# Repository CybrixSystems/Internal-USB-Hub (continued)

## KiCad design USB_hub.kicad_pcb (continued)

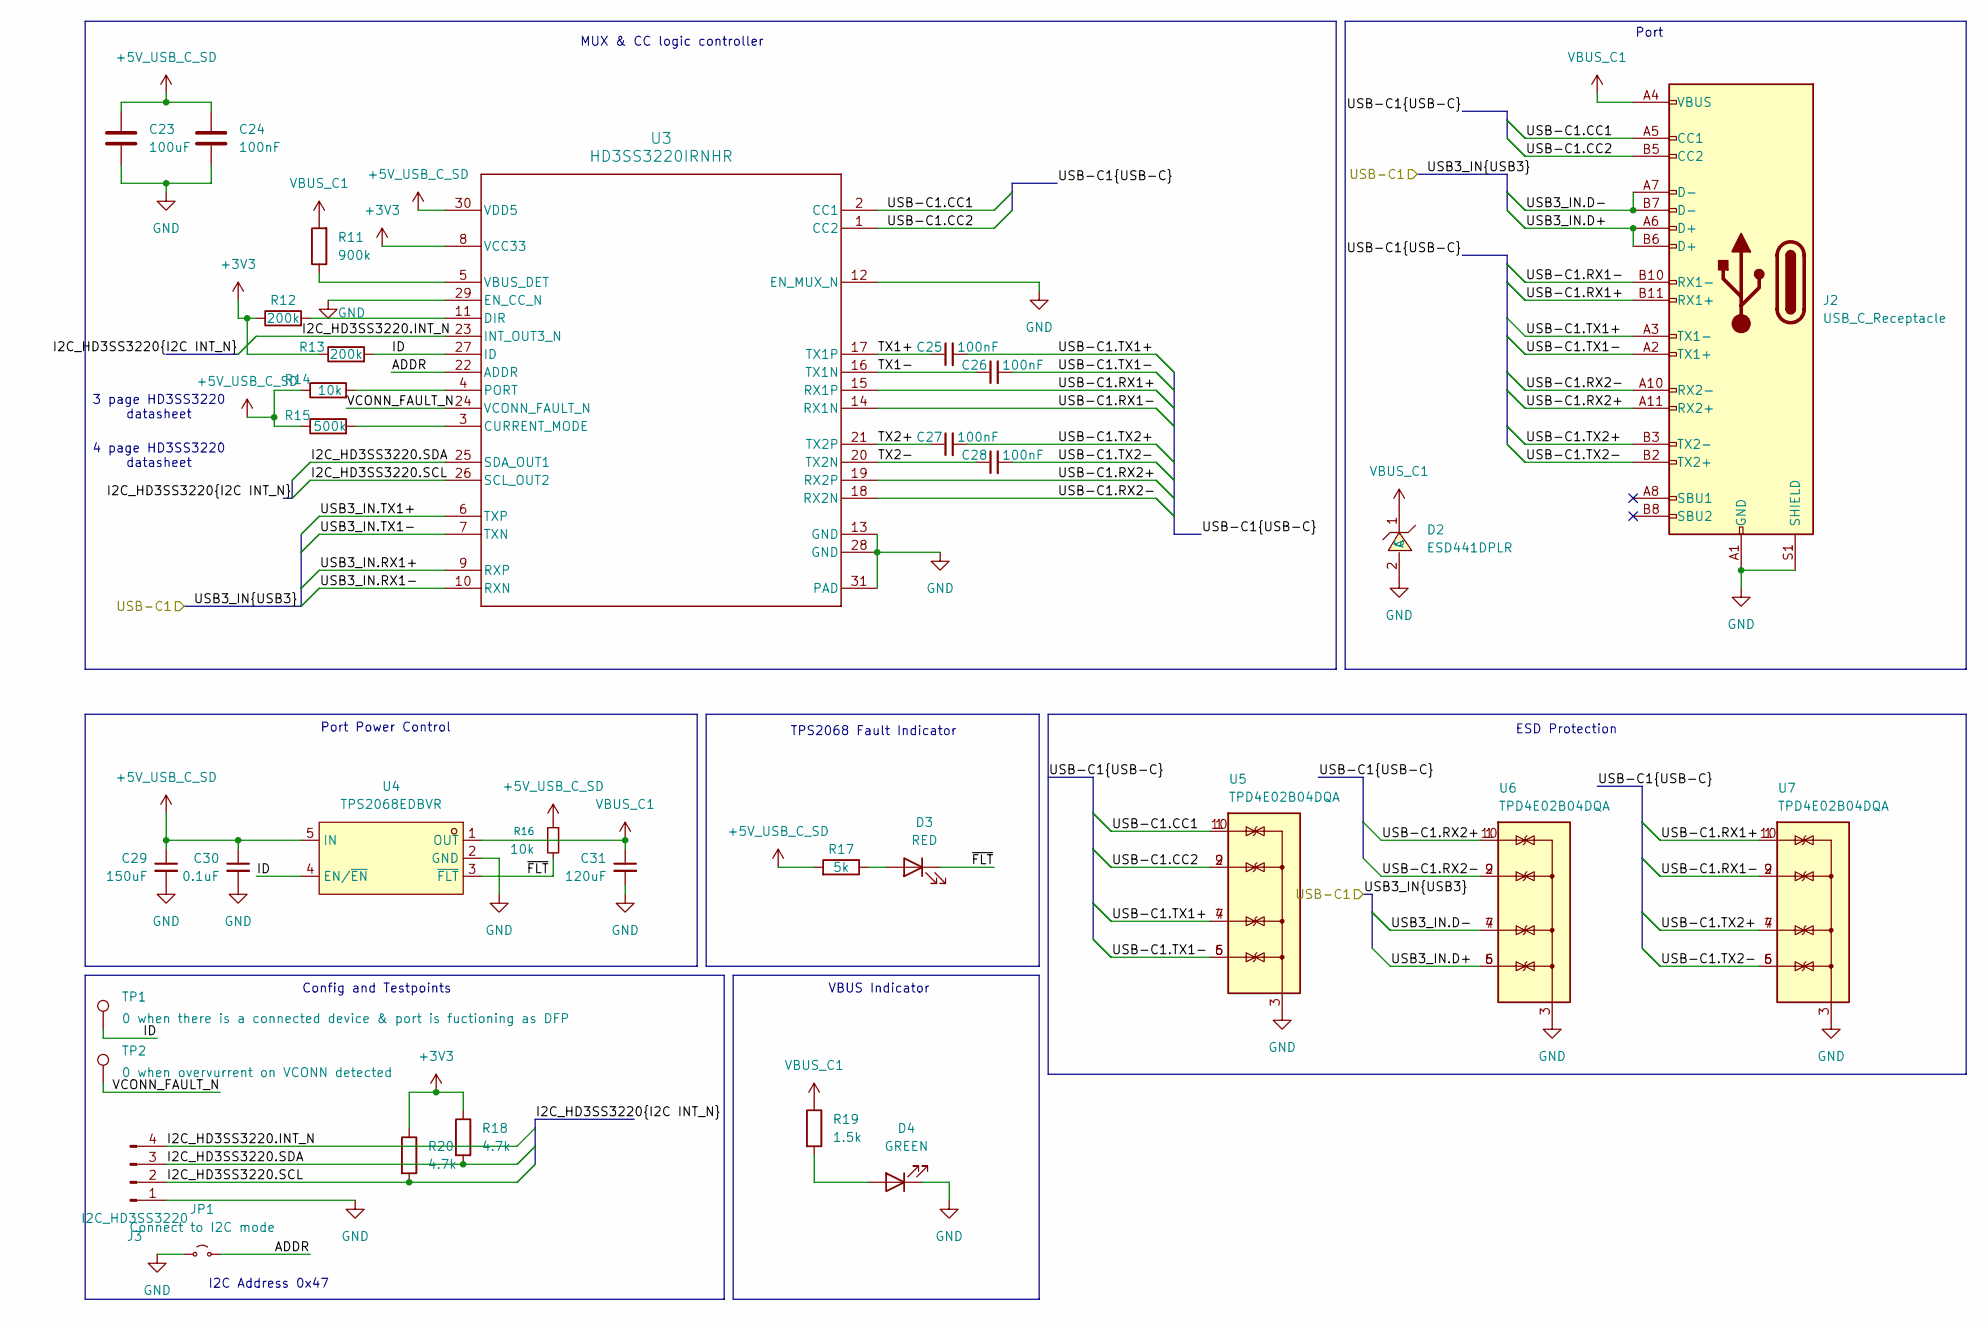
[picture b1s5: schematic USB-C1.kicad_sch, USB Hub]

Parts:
C23: 100uF; C_0805_2012Metric; LCSC Part C141660
C24, C25, C26, C27, C28: 100nF; C_0201_0603Metric; LCSC Part C181043
C29: 150uF; C_Radial_D6.3mm_H11.0mm_P2.50mm; LCSC Part C338186
C30: 0.1uF; C_0201_0603Metric; LCSC Part C181043
C31: 120uF; C_Radial_D6.3mm_H11.0mm_P2.50mm; LCSC Part C442816
D2: ESD441DPLR; X2SON-2_L0.6-W0.3-P0.35; LCSC Part C22427765
D3: RED; LED_0603_1608Metric; LCSC Part C497918
D4: GREEN; LED_0603_1608Metric; LCSC Part C22371298
J2: USB_C_Receptacle; USB420003A; Mouser Part No 640-USB4200-03-A
J3: I2C_HD3SS3220; PinHeader_1x04_P1.00mm_Vertical
JP1: Connect to I2C mode; SolderJumper-2_P1.3mm_Open_Pad1.0x1.5mm
R11: 900k; R_1206_3216Metric; Mouser Part No 603-RT1206CRE07900KL
R12, R13: 200k; R_0402_1005Metric; LCSC Part C25764
R14, R16: 10k; R_0402_1005Metric; LCSC Part C25744
R15: 500k; R_0603_1608Metric; LCSC Part C2902631
R17: 5k; R_0402_1005Metric; LCSC Part C5948099
R18, R20: 4.7k; R_0402_1005Metric; LCSC Part C105871
R19: 1.5k; R_0402_1005Metric; LCSC Part C327253
TP1: 0 when there is a connected device & port is fuct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; TestPoint_Pad_D1.0mm
TP2: 0 when overvurrent on VCONN detected; TestPoint_Pad_D1.0mm
U3: HD3SS3220IRNHR; RNH0030A; LCSC Part C165155
U4: TPS2068EDBVR; TSOT-23-5_L2.9-W1.6-P0.95-LS2.8-BR; LCSC Part C19272843
U5, U6, U7: TPD4E02B04DQA; USON-10_2.5x1.0mm_P0.5mm; LCSC Part C106794

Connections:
+3V3: R12.1, R13.1, R18.1, R20.1, U3.8 (VCC33); also elsewhere on the board
+5V_USB_C_SD: C23.1, C24.1, C29.1, C30.1, R14.1, R15.1, R16.1, R17.2, U3.30 (VDD5), U4.5 (IN); also elsewhere on the board
/USB-C1/ADDR: JP1.2 (B), U3.22 (ADDR)
/USB-C1/I2C_HD3SS3220.INT_N: J3.4, U3.23 (INT_OUT3_N)
/USB-C1/I2C_HD3SS3220.SCL: J3.2, R20.2, U3.26 (SCL_OUT2)
/USB-C1/I2C_HD3SS3220.SDA: J3.3, R18.2, U3.25 (SDA_OUT1)
/USB-C1/ID: R13.2, TP1.1, U3.27 (ID), U4.4 (EN/~EN)
/USB-C1/TX1+: C25.1, U3.17 (TX1P)
/USB-C1/TX1-: C26.1, U3.16 (TX1N)
/USB-C1/TX2+: C27.1, U3.21 (TX2P)
/USB-C1/TX2-: C28.1, U3.20 (TX2N)
/USB-C1/USB3_IN.D+: J2.A6 (D+), J2.B6 (D+), U6.5 (IO4), U6.6 (NC); also elsewhere on the board
/USB-C1/USB3_IN.D-: J2.A7 (D-), J2.B7 (D-), U6.4 (IO3), U6.7 (NC); also elsewhere on the board
/USB-C1/USB3_IN.RX1+: U3.9 (RXP); also elsewhere on the board
/USB-C1/USB3_IN.RX1-: U3.10 (RXN); also elsewhere on the board
/USB-C1/USB3_IN.TX1+: U3.6 (TXP); also elsewhere on the board
/USB-C1/USB3_IN.TX1-: U3.7 (TXN)
/USB-C1/USB-C1.CC1: J2.A5 (CC1), U3.2 (CC1), U5.1 (IO1), U5.10 (NC)
/USB-C1/USB-C1.CC2: J2.B5 (CC2), U3.1 (CC2), U5.2 (IO2), U5.9 (NC)
/USB-C1/USB-C1.RX1+: J2.B11 (RX1+), U3.15 (RX1P), U7.1 (IO1), U7.10 (NC)
/USB-C1/USB-C1.RX1-: J2.B10 (RX1-), U3.14 (RX1N), U7.2 (IO2), U7.9 (NC)
/USB-C1/USB-C1.RX2+: J2.A11 (RX2+), U3.19 (RX2P), U6.1 (IO1), U6.10 (NC)
/USB-C1/USB-C1.RX2-: J2.A10 (RX2-), U3.18 (RX2N), U6.2 (IO2), U6.9 (NC)
/USB-C1/USB-C1.TX1+: C25.2, J2.A3 (TX1-), U5.4 (IO3), U5.7 (NC)
/USB-C1/USB-C1.TX1-: C26.2, J2.A2 (TX1+), U5.5 (IO4), U5.6 (NC)
/USB-C1/USB-C1.TX2+: C27.2, J2.B3 (TX2-), U7.4 (IO3), U7.7 (NC)
/USB-C1/USB-C1.TX2-: C28.2, J2.B2 (TX2+), U7.5 (IO4), U7.6 (NC)
/USB-C1/VCONN_FAULT_N: TP2.1, U3.24 (VCONN_FAULT_N)
/USB-C1/~FLT: D3.1 (K), R16.2, U4.3 (~FLT)
GND: C23.2, C24.2, C29.2, C30.2, C31.2, D2.2 (A), D4.1 (K), J2.A1 (GND), J2.A12 (GND), J2.B1 (GND), J2.B12 (GND), J2.S1 (SHIELD), J3.1, JP1.1 (A), U3.12 (EN_MUX_N), U3.13 (GND), U3.28 (GND), U3.29 (EN_CC_N), U3.31 (PAD), U4.2 (GND), U5.3 (G), U5.8 (G), U6.3 (G), U6.8 (G), U7.3 (G), U7.8 (G); also elsewhere on the board
unnamed: D3.2 (A), R17.1
unnamed: D4.2 (A), R19.2
unnamed: R15.2, U3.3 (CURRENT_MODE)
unnamed: R12.2, U3.11 (DIR)
unnamed: R14.2, U3.4 (PORT)
unnamed: R11.1, U3.5 (VBUS_DET)
VBUS_C1: C31.1, D2.1 (C), J2.A4 (VBUS), J2.A9 (VBUS), J2.B4 (VBUS), J2.B9 (VBUS), R11.2, R19.1, U4.1 (OUT); also elsewhere on the board

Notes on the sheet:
TPS2068 Fault Indicator
4 page HD3SS3220 datasheet
I2C Address 0x47
3 page HD3SS3220 datasheet
Port
VBUS Indicator
Config and Testpoints
Port Power Control
ESD Protection
MUX & CC logic controller

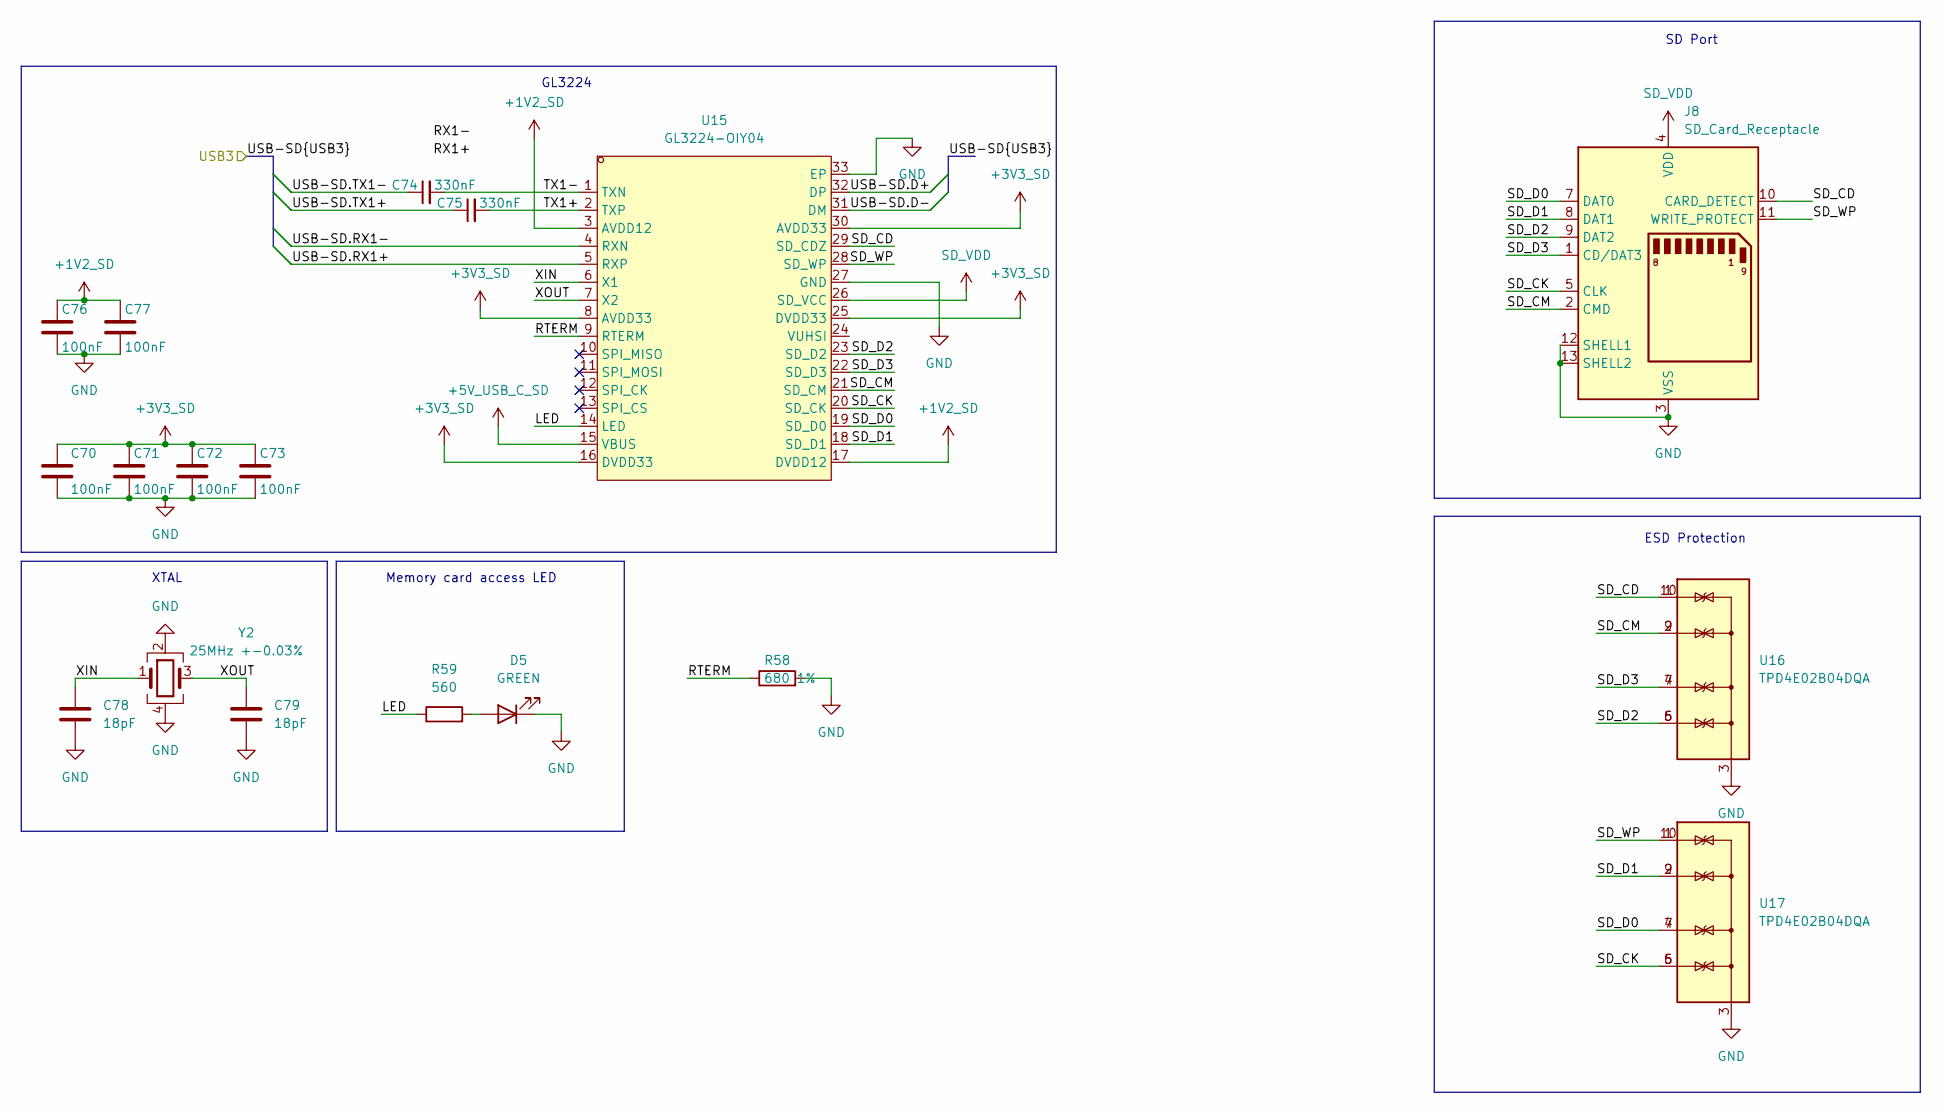
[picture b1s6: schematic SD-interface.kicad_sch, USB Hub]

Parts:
C70, C71, C72, C73, C76, C77: 100nF; C_0201_0603Metric; LCSC Part C181043
C74, C75: 330nF; C_0201_0603Metric; LCSC Part C2980695
C78, C79: 18pF; C_0402_1005Metric; LCSC Part C33149
D5: GREEN; LED_0603_1608Metric; LCSC Part C22371298
J8: SD_Card_Receptacle; SD2A; Mouser Part No 179-SD-2-A
R58: 680 1%; R_0402_1005Metric; LCSC Part C25130
R59: 560; R_0402_1005Metric; LCSC Part C137858
U15: GL3224-OIY04; HQFN-32_L5.0-W5.0-P0.50-BL-EP3.0; LCSC Part C157357
U16, U17: TPD4E02B04DQA; USON-10_2.5x1.0mm_P0.5mm; LCSC Part C106794
Y2: 25MHz +-0.03%; Crystal_SMD_3225-4Pin_3.2x2.5mm; LCSC Part C179643

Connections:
+1V2_SD: C76.1, C77.1, U15.3 (AVDD12), U15.17 (DVDD12)
+3V3_SD: C70.1, C71.1, C72.1, C73.1, U15.8 (AVDD33), U15.16 (DVDD33), U15.25 (DVDD33), U15.30 (AVDD33)
+5V_USB_C_SD: U15.15 (VBUS); also elsewhere on the board
/SD-interface/LED: R59.1, U15.14 (LED)
/SD-interface/RTERM: R58.1, U15.9 (RTERM)
/SD-interface/SD_CD: J8.10 (CARD_DETECT), U15.29 (SD_CDZ), U16.1 (IO1), U16.10 (NC)
/SD-interface/SD_CK: J8.5 (CLK), U15.20 (SD_CK), U17.5 (IO4), U17.6 (NC)
/SD-interface/SD_CM: J8.2 (CMD), U15.21 (SD_CM), U16.2 (IO2), U16.9 (NC)
/SD-interface/SD_D0: J8.7 (DAT0), U15.19 (SD_D0), U17.4 (IO3), U17.7 (NC)
/SD-interface/SD_D1: J8.8 (DAT1), U15.18 (SD_D1), U17.2 (IO2), U17.9 (NC)
/SD-interface/SD_D2: J8.9 (DAT2), U15.23 (SD_D2), U16.5 (IO4), U16.6 (NC)
/SD-interface/SD_D3: J8.1 (CD/DAT3), U15.22 (SD_D3), U16.4 (IO3), U16.7 (NC)
/SD-interface/SD_WP: J8.11 (WRITE_PROTECT), U15.28 (SD_WP), U17.1 (IO1), U17.10 (NC)
/SD-interface/TX1+: C75.2, U15.2 (TXP)
/SD-interface/TX1-: C74.2, U15.1 (TXN)
/SD-interface/USB-SD.D+: U15.32 (DP); also elsewhere on the board
/SD-interface/USB-SD.D-: U15.31 (DM); also elsewhere on the board
/SD-interface/USB-SD.RX1+: U15.5 (RXP); also elsewhere on the board
/SD-interface/USB-SD.RX1-: U15.4 (RXN); also elsewhere on the board
/SD-interface/USB-SD.TX1+: C75.1; also elsewhere on the board
/SD-interface/USB-SD.TX1-: C74.1; also elsewhere on the board
/SD-interface/XIN: C78.2, U15.6 (X1), Y2.1
/SD-interface/XOUT: C79.2, U15.7 (X2), Y2.3
GND: C70.2, C71.2, C72.2, C73.2, C76.2, C77.2, C78.1, C79.1, D5.1 (K), J8.3 (VSS), J8.6 (VSS), J8.12 (SHELL1), J8.13 (SHELL2), R58.2, U15.27 (GND), U15.33 (EP), U16.3 (G), U16.8 (G), U17.3 (G), U17.8 (G), Y2.2, Y2.4; also elsewhere on the board
unnamed: D5.2 (A), R59.2
SD_VDD: J8.4 (VDD), U15.26 (SD_VCC)

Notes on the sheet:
Memory card access LED
ESD Protection
SD Port
GL3224
XTAL

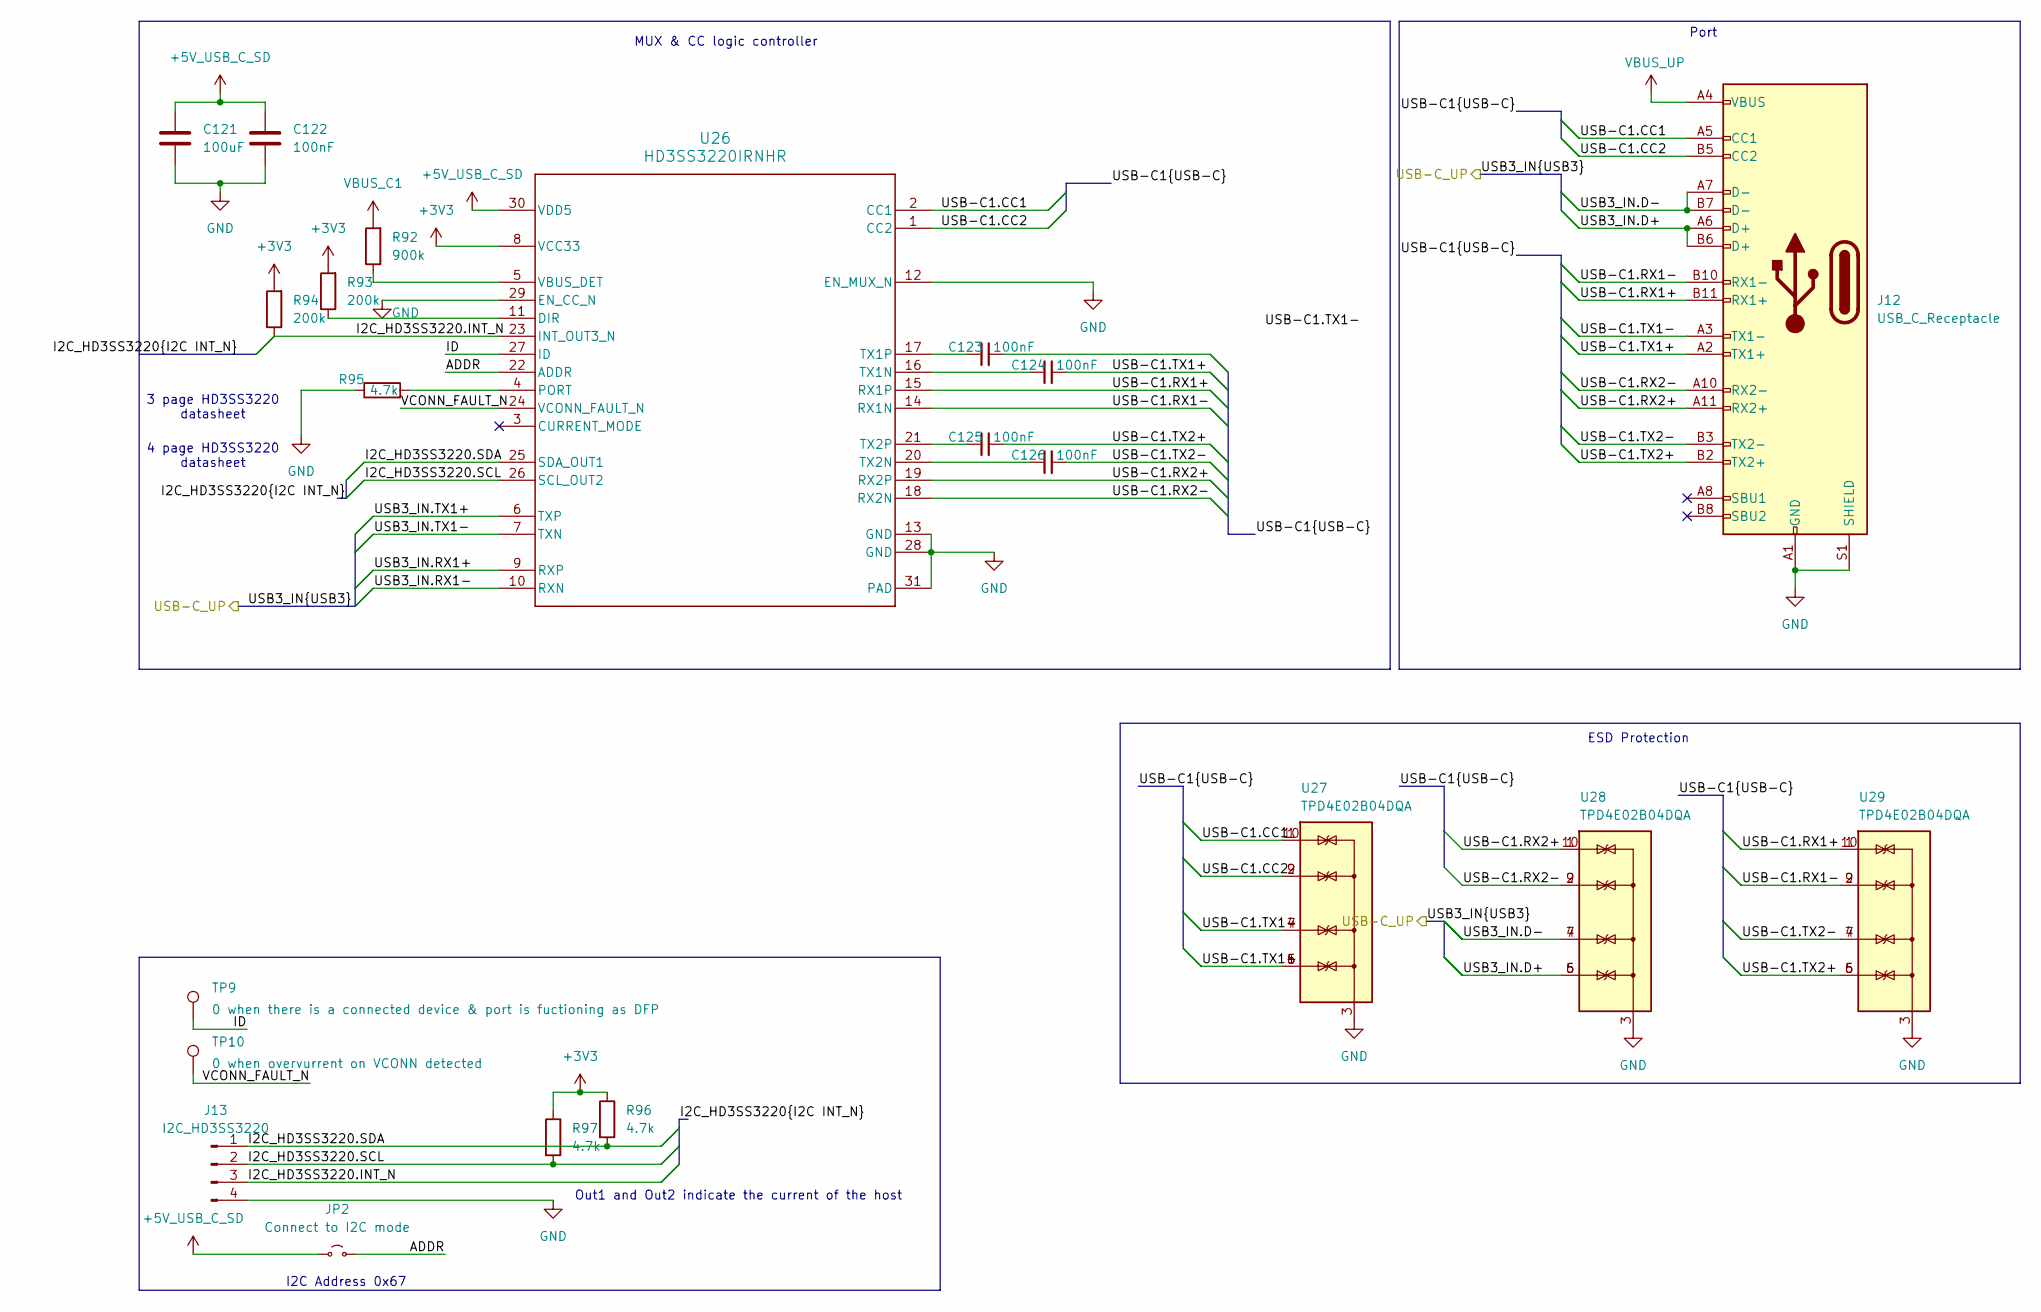
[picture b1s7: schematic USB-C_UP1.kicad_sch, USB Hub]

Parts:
C121: 100uF; C_0805_2012Metric; LCSC Part C141660
C122, C123, C124, C125, C126: 100nF; C_0201_0603Metric; LCSC Part C181043
J12: USB_C_Receptacle; USB_C_Receptacle_Amphenol_12401610E4-2A
J13: I2C_HD3SS3220; PinHeader_1x03_P1.00mm_Vertical
JP2: Connect to I2C mode; SolderJumper-2_P1.3mm_Open_RoundedPad1.0x1.5mm
R92: 900k; R_1206_3216Metric; Mouser Part No 603-RT1206CRE07900KL
R93, R94: 200k; R_0402_1005Metric; LCSC Part C25764
R95, R96, R97: 4.7k; R_0402_1005Metric; LCSC Part C105871
TP9: 0 when there is a connected device & port is fuct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; TestPoint_Pad_D1.0mm
TP10: 0 when overvurrent on VCONN detected; TestPoint_Pad_D1.0mm
U26: HD3SS3220IRNHR; RNH0030A; LCSC Part C165155
U27, U28, U29: TPD4E02B04DQA; USON-10_2.5x1.0mm_P0.5mm; LCSC Part C106794

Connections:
+3V3: R93.2, R94.2, R96.1, R97.1, U26.8 (VCC33); also elsewhere on the board
+5V_USB_C_SD: C121.1, C122.1, JP2.1 (A), U26.30 (VDD5); also elsewhere on the board
/USB-C_UP1/ADDR: JP2.2 (B), U26.22 (ADDR)
/USB-C_UP1/I2C_HD3SS3220.INT_N: J13.3, R94.1, U26.23 (INT_OUT3_N)
/USB-C_UP1/I2C_HD3SS3220.SCL: J13.2, R97.2, U26.26 (SCL_OUT2)
/USB-C_UP1/I2C_HD3SS3220.SDA: J13.1, R96.2, U26.25 (SDA_OUT1)
/USB-C_UP1/ID: TP9.1, U26.27 (ID)
/USB-C_UP1/USB3_IN.D+: J12.A6 (D+), J12.B6 (D+), U28.5 (IO4), U28.6 (NC); also elsewhere on the board
/USB-C_UP1/USB3_IN.D-: J12.A7 (D-), J12.B7 (D-), U28.4 (IO3), U28.7 (NC); also elsewhere on the board
/USB-C_UP1/USB3_IN.RX1+: U26.9 (RXP); also elsewhere on the board
/USB-C_UP1/USB3_IN.RX1-: U26.10 (RXN); also elsewhere on the board
/USB-C_UP1/USB3_IN.TX1+: U26.6 (TXP); also elsewhere on the board
/USB-C_UP1/USB3_IN.TX1-: U26.7 (TXN); also elsewhere on the board
/USB-C_UP1/USB-C1.CC1: J12.A5 (CC1), U26.2 (CC1), U27.1 (IO1), U27.10 (NC)
/USB-C_UP1/USB-C1.CC2: J12.B5 (CC2), U26.1 (CC2), U27.2 (IO2), U27.9 (NC)
/USB-C_UP1/USB-C1.RX1+: J12.B11 (RX1+), U26.15 (RX1P), U29.1 (IO1), U29.10 (NC)
/USB-C_UP1/USB-C1.RX1-: J12.B10 (RX1-), U26.14 (RX1N), U29.2 (IO2), U29.9 (NC)
/USB-C_UP1/USB-C1.RX2+: J12.A11 (RX2+), U26.19 (RX2P), U28.1 (IO1), U28.10 (NC)
/USB-C_UP1/USB-C1.RX2-: J12.A10 (RX2-), U26.18 (RX2N), U28.2 (IO2), U28.9 (NC)
/USB-C_UP1/USB-C1.TX1+: C124.2, J12.A2 (TX1+), U27.5 (IO4), U27.6 (NC)
/USB-C_UP1/USB-C1.TX1-: J12.A3 (TX1-), U27.4 (IO3), U27.7 (NC)
/USB-C_UP1/USB-C1.TX2+: C125.2, J12.B2 (TX2+), U29.5 (IO4), U29.6 (NC)
/USB-C_UP1/USB-C1.TX2-: C126.2, J12.B3 (TX2-), U29.4 (IO3), U29.7 (NC)
/USB-C_UP1/VCONN_FAULT_N: TP10.1, U26.24 (VCONN_FAULT_N)
GND: C121.2, C122.2, J12.A1 (GND), J12.A12 (GND), J12.B1 (GND), J12.B12 (GND), J12.S1 (SHIELD), J13.4, R95.1, U26.12 (EN_MUX_N), U26.13 (GND), U26.28 (GND), U26.29 (EN_CC_N), U26.31 (PAD), U27.3 (G), U27.8 (G), U28.3 (G), U28.8 (G), U29.3 (G), U29.8 (G); also elsewhere on the board
unnamed: R93.1, U26.11 (DIR)
unnamed: R95.2, U26.4 (PORT)
unnamed: C124.1, U26.16 (TX1N)
unnamed: C123.1, U26.17 (TX1P)
unnamed: C126.1, U26.20 (TX2N)
unnamed: C125.1, U26.21 (TX2P)
unnamed: R92.1, U26.5 (VBUS_DET)
VBUS_C1: R92.2; also elsewhere on the board
VBUS_UP: J12.A4 (VBUS), J12.A9 (VBUS), J12.B4 (VBUS), J12.B9 (VBUS); also elsewhere on the board

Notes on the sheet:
4 page HD3SS3220 datasheet
3 page HD3SS3220 datasheet
Port
Out1 and Out2 indicate the current of the host
I2C Address 0x67
ESD Protection
MUX & CC logic controller

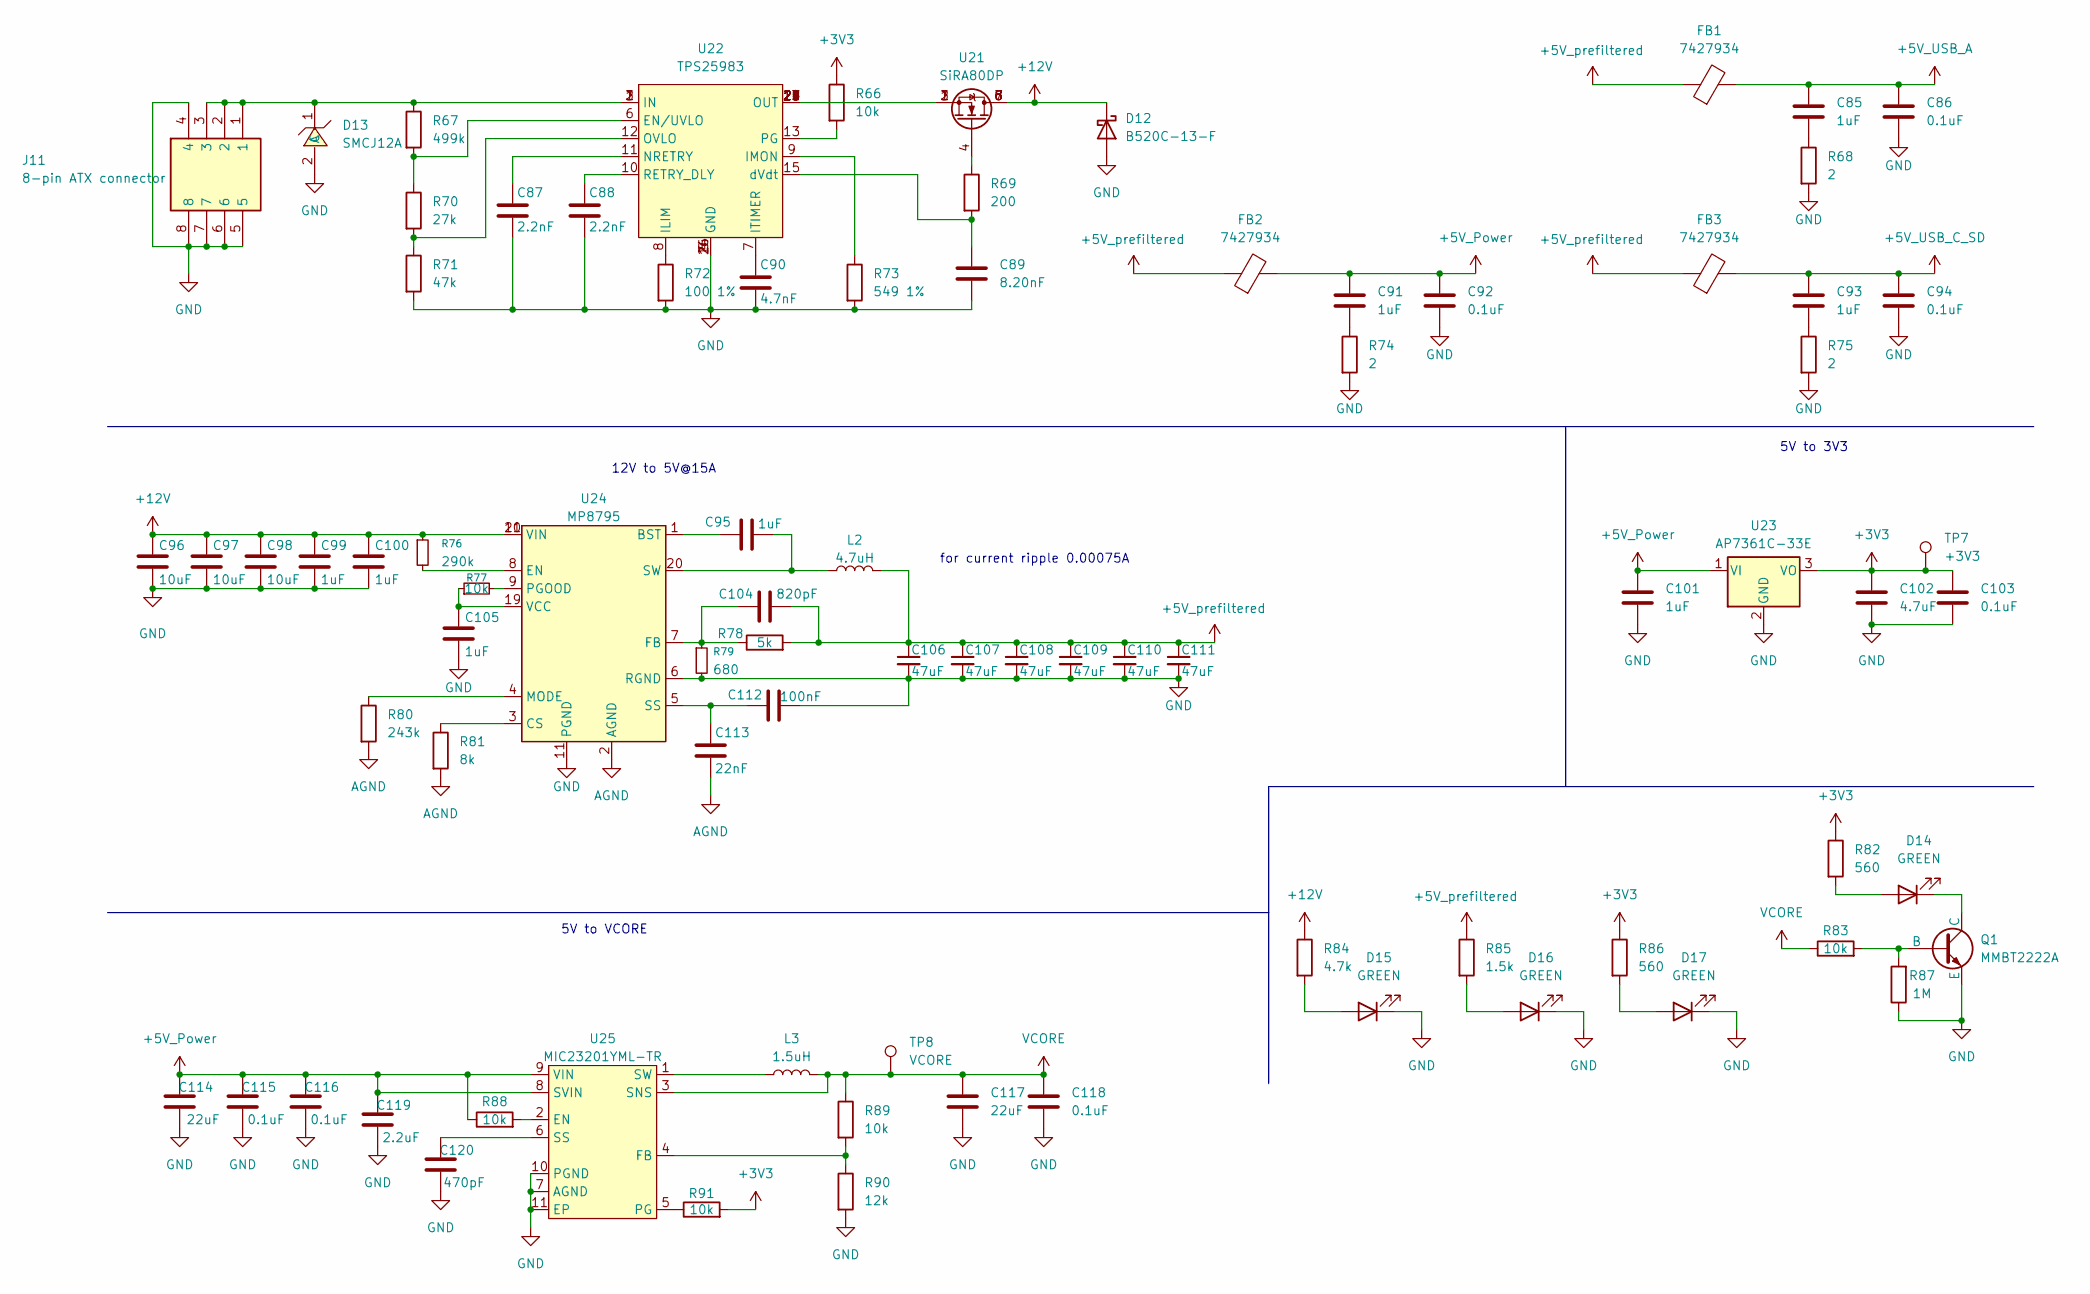
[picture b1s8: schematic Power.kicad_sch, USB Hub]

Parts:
C85, C91, C93, C95, C99, C100, C101, C105: 1uF; C_0603_1608Metric; LCSC Part C5199872
C86, C92, C94, C103, C115, C116, C118: 0.1uF; C_0201_0603Metric; LCSC Part C181043
C87, C88: 2.2nF; C_0402_1005Metric; LCSC Part C513667
C89: 8.20nF; C_0402_1005Metric; LCSC Part C541457
C90: 4.7nF; C_0402_1005Metric; LCSC Part C281757
C96, C97, C98: 10uF; C_0805_2012Metric; LCSC Part C3039694
C102: 4.7uF; C_0805_2012Metric; LCSC Part C6119944
C104: 820pF; C_0402_1005Metric; LCSC Part C114386
C106, C107, C108, C109, C110, C111: 47uF; C_Radial_D5.0mm_H11.0mm_P2.00mm; LCSC Part C721300
C112: 100nF; C_0201_0603Metric; LCSC Part C181043
C113: 22nF; C_0402_1005Metric; LCSC Part C77023
C114, C117: 22uF; C_1812_4532Metric; LCSC Part C141660
C119: 2.2uF; C_0402_1005Metric; LCSC Part C2999759
C120: 470pF; C_0402_1005Metric; LCSC Part C272887
D12: B520C-13-F; D_SMC; LCSC Part C134460
D13: SMCJ12A; D_SMC; LCSC Part C224038
D14, D15, D16, D17: GREEN; LED_0603_1608Metric; LCSC Part C22371298
FB1, FB2, FB3: 7427934; Mouser Part No 710-7427934; LCSC Part C5429469
J11: 8-pin ATX connector; 45586-000Y; Manufacturer_Part_Number 45586-0005; Mouser Part No 538-45586-0005
L2: 4.7uH; L_Coilcraft_XAL1010-XXX; LCSC Part C18199458
L3: 1.5uH; L_6.3x6.3_H3; LCSC Part C520330
Q1: MMBT2222A; SOT-23-3; LCSC Part C82460
R66, R77, R83, R88, R89, R91: 10k; R_0402_1005Metric; LCSC Part C25744
R67: 499k; R_0402_1005Metric; LCSC Part C137971
R68, R74, R75: 2; R_0603_1608Metric; LCSC Part C2907139
R69: 200; R_0402_1005Metric; LCSC Part C114764
R70: 27k; R_0402_1005Metric; LCSC Part C138022
R71: 47k; R_0402_1005Metric; LCSC Part C93943
R72: 100 1%; R_0402_1005Metric; LCSC Part C106232
R73: 549 1%; R_0402_1005Metric; LCSC Part C7334458
R76: 290k; R_0402_1005Metric; LCSC Part C5126158
R78: 5k; R_0402_1005Metric; LCSC Part C5948099
R79: 680; R_0402_1005Metric; LCSC Part C25130
R80: 243k; R_0402_1005Metric; LCSC Part C2998149
R81: 8k; R_0603_1608Metric; LCSC Part C862307
R82, R86: 560; R_0402_1005Metric; LCSC Part C137858
R84: 4.7k; R_0402_1005Metric; LCSC Part C105871
R85: 1.5k; R_0402_1005Metric; LCSC Part C327253
R87: 1M; R_0402_1005Metric; LCSC Part C2906900
R90: 12k; R_0402_1005Metric; LCSC Part C413006
TP7: +3V3; TestPoint_Pad_D1.0mm
TP8: VCORE; TestPoint_Pad_D1.0mm
U21: SiRA80DP; PowerPAK_SO-8L_Single; Mouser Part No 78-SIRA80DP-T1-RE3; LCSC Part C3289458
U22: TPS25983; TPS259830ONRGER; LCSC Part C20611808
U23: AP7361C-33E; SOT-223-3_TabPin2; LCSC Part C500795
U24: MP8795; MPS-QFN-21_3x4mm; LCSC Part C3188708
U25: MIC23201YML-TR; TDFN-10_L3.0-W3.0-P0.50-TL-EP; Mouser Part No 998-MIC23201YMLTR; LCSC Part C621769

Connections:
+3V3: C102.1, C103.1, R66.1, R82.1, R86.1, R91.2, TP7.1, U23.3 (VO); also elsewhere on the board
+5V_Power: C91.1, C92.1, C101.1, C114.1, C115.1, C116.1, C119.1, FB2.2, R88.1, U23.1 (VI), U25.8 (SVIN), U25.9 (VIN)
+5V_USB_A: C85.1, C86.1, FB1.2; also elsewhere on the board
+5V_USB_C_SD: C93.1, C94.1, FB3.2; also elsewhere on the board
+5V_prefiltered: C104.2, C106.1, C107.1, C108.1, C109.1, C110.1, C111.1, FB1.1, FB2.1, FB3.1, L2.2, R78.2, R85.1
+12V: C96.1, C97.1, C98.1, C99.1, C100.1, D12.1 (K), R76.1, R84.1, U21.5 (D), U21.6 (D), U21.7 (D), U21.8 (D), U24.10 (VIN), U24.21 (VIN); also elsewhere on the board
AGND: C113.2, R80.2, R81.2, U24.2 (AGND)
GND: C86.2, C87.2, C88.2, C89.2, C90.2, C92.2, C94.2, C96.2, C97.2, C98.2, C99.2, C100.2, C101.2, C102.2, C103.2, C105.2, C106.2, C107.2, C108.2, C109.2, C110.2, C111.2, C112.2, C114.2, C115.2, C116.2, C117.2, C118.2, C119.2, C120.2, D12.2 (A), D13.2 (A), D15.1 (K), D16.1 (K), D17.1 (K), J11.4, J11.5, J11.6, J11.7, J11.8, Q1.3 (E), R68.2, R71.2, R72.2, R73.2, R74.2, R75.2, R79.2, R87.1, R90.2, U22.4 (GND), U22.5 (GND), U22.14 (GND), U22.26 (GND), U23.2 (GND), U24.6 (RGND), U24.11 (PGND), U25.7 (AGND), U25.10 (PGND), U25.11 (EP); also elsewhere on the board
unnamed: C85.2, R68.1
unnamed: C91.2, R74.1
unnamed: C93.2, R75.1
unnamed: D13.1 (C), J11.1, J11.2, J11.3, R67.1, U22.1 (IN), U22.2 (IN), U22.3 (IN)
unnamed: D14.2 (A), R82.2
unnamed: D14.1 (K), Q1.1 (C)
unnamed: D15.2 (A), R84.2
unnamed: D16.2 (A), R85.2
unnamed: D17.2 (A), R86.2
unnamed: Q1.2 (B), R83.2, R87.2
unnamed: R69.1, U21.4 (G)
unnamed: U21.1 (S), U21.2 (S), U21.3 (S), U22.17 (OUT), U22.18 (OUT), U22.19 (OUT), U22.20 (OUT), U22.21 (OUT), U22.22 (OUT), U22.23 (OUT), U22.24 (OUT), U22.25 (OUT)
unnamed: R67.2, R70.1, U22.6 (EN/UVLO)
unnamed: R72.1, U22.8 (ILIM)
unnamed: R73.1, U22.9 (IMON)
unnamed: C90.1, U22.7 (ITIMER)
unnamed: C87.1, U22.11 (NRETRY)
unnamed: R70.2, R71.1, U22.12 (OVLO)
unnamed: R66.2, U22.13 (PG)
unnamed: C88.1, U22.10 (RETRY_DLY)
unnamed: C89.1, R69.2, U22.15 (dVdt)
unnamed: C95.1, U24.1 (BST)
unnamed: R81.1, U24.3 (CS)
unnamed: R76.2, U24.8 (EN)
unnamed: C104.1, R78.1, R79.1, U24.7 (FB)
unnamed: R80.1, U24.4 (MODE)
unnamed: R77.2, U24.9 (PGOOD)
unnamed: C112.1, C113.1, U24.5 (SS)
unnamed: C95.2, L2.1, U24.20 (SW)
unnamed: C105.1, R77.1, U24.19 (VCC)
unnamed: R88.2, U25.2 (EN)
unnamed: R89.2, R90.1, U25.4 (FB)
unnamed: R91.1, U25.5 (PG)
unnamed: C120.1, U25.6 (SS)
unnamed: L3.1, U25.1 (SW)
VCORE: C117.1, C118.1, L3.2, R83.1, R89.1, TP8.1, U25.3 (SNS); also elsewhere on the board

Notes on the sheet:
5V to VCORE
12V to 5V@15A
5V to 3V3
for current ripple 0.00075A

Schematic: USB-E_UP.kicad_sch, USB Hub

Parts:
J14: USB_C_Internal_Connector
R98, R99: 5.1k; LCSC Part C2906948
U30, U31: TPD4E02B04DQA; USON-10_2.5x1.0mm_P0.5mm; LCSC Part C106794

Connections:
unnamed: J14.18 (D-), U30.1 (IO1), U30.10 (NC)
unnamed: J14.P1 (VBUS), J14.P7 (VBUS), J14.P11 (VBUS)
unnamed: J14.P2 (TX1+), U31.5 (IO4), U31.6 (NC)
unnamed: J14.P3 (TX1-), U31.4 (IO3), U31.7 (NC)
unnamed: J14.P5 (RX1+), U31.2 (IO2), U31.9 (NC)
unnamed: J14.P6 (RX1-), U31.1 (IO1), U31.10 (NC)
unnamed: J14.P8 (CC1), R98.1
unnamed: J14.P4 (GND), J14.P14 (GND), J14.P17 (GND), J14.S1 (SHIELD), R98.2, R99.2, U30.3 (G), U30.8 (G), U31.3 (G), U31.8 (G)
unnamed: J14.P19 (D+), U30.2 (IO2), U30.9 (NC)
unnamed: J14.P20 (CC2), R99.1
unnamed: U30.4 (IO3), U30.7 (NC)
unnamed: U30.5 (IO4), U30.6 (NC)

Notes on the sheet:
USB Connector

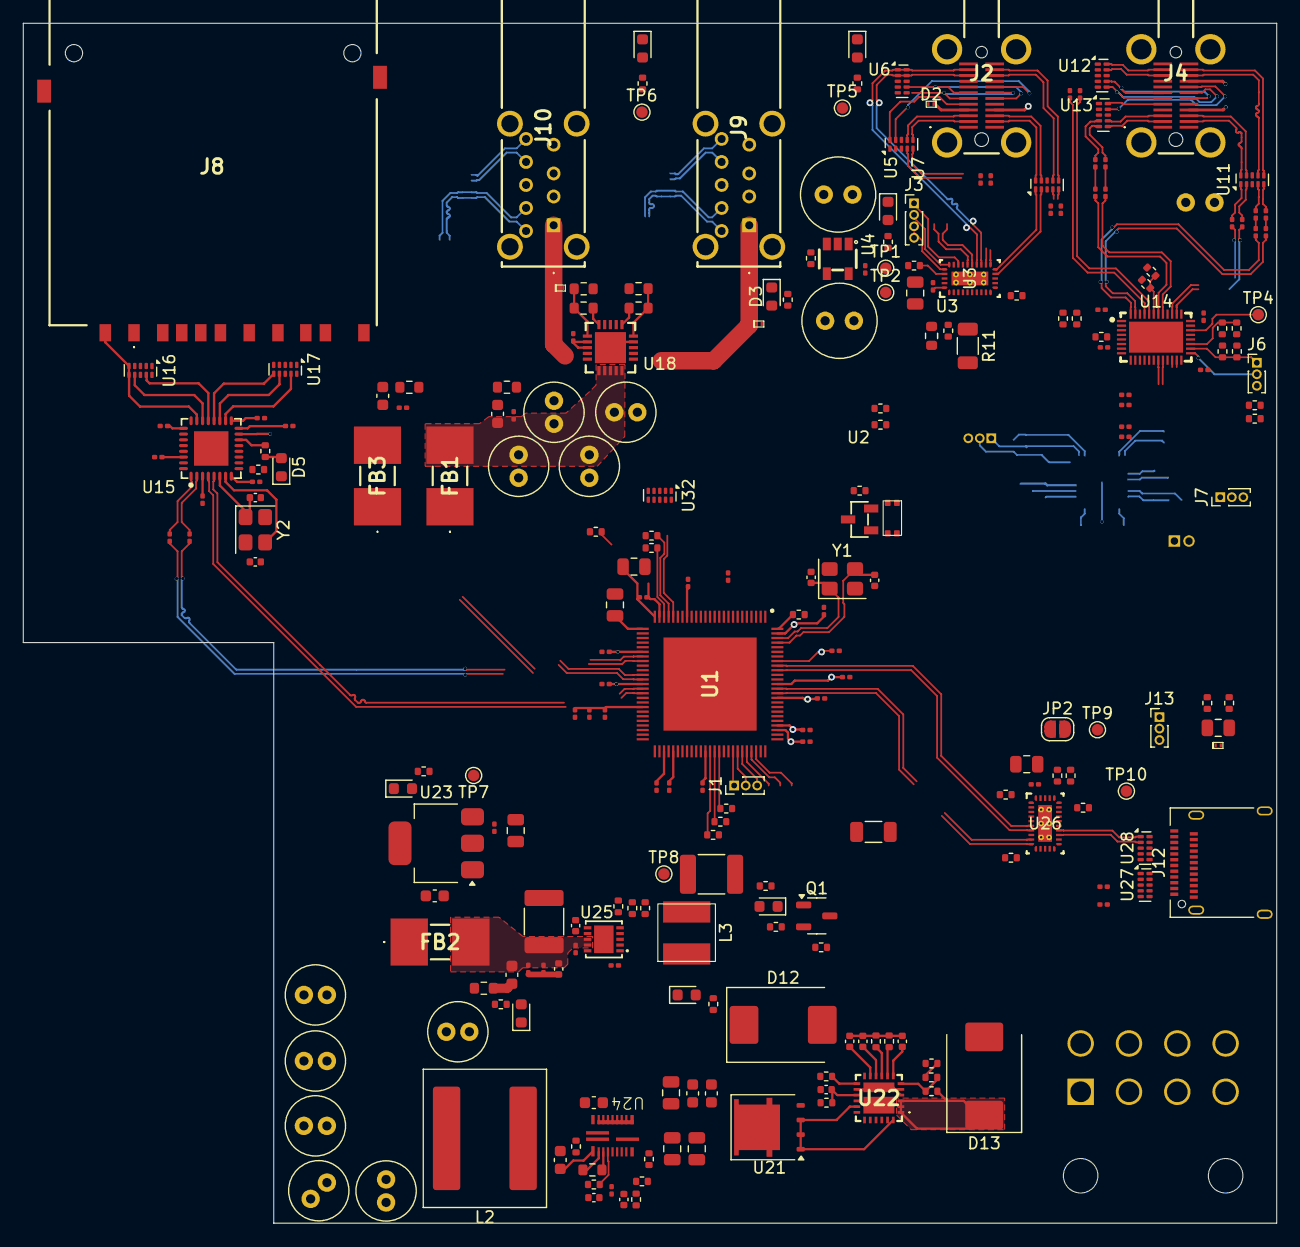
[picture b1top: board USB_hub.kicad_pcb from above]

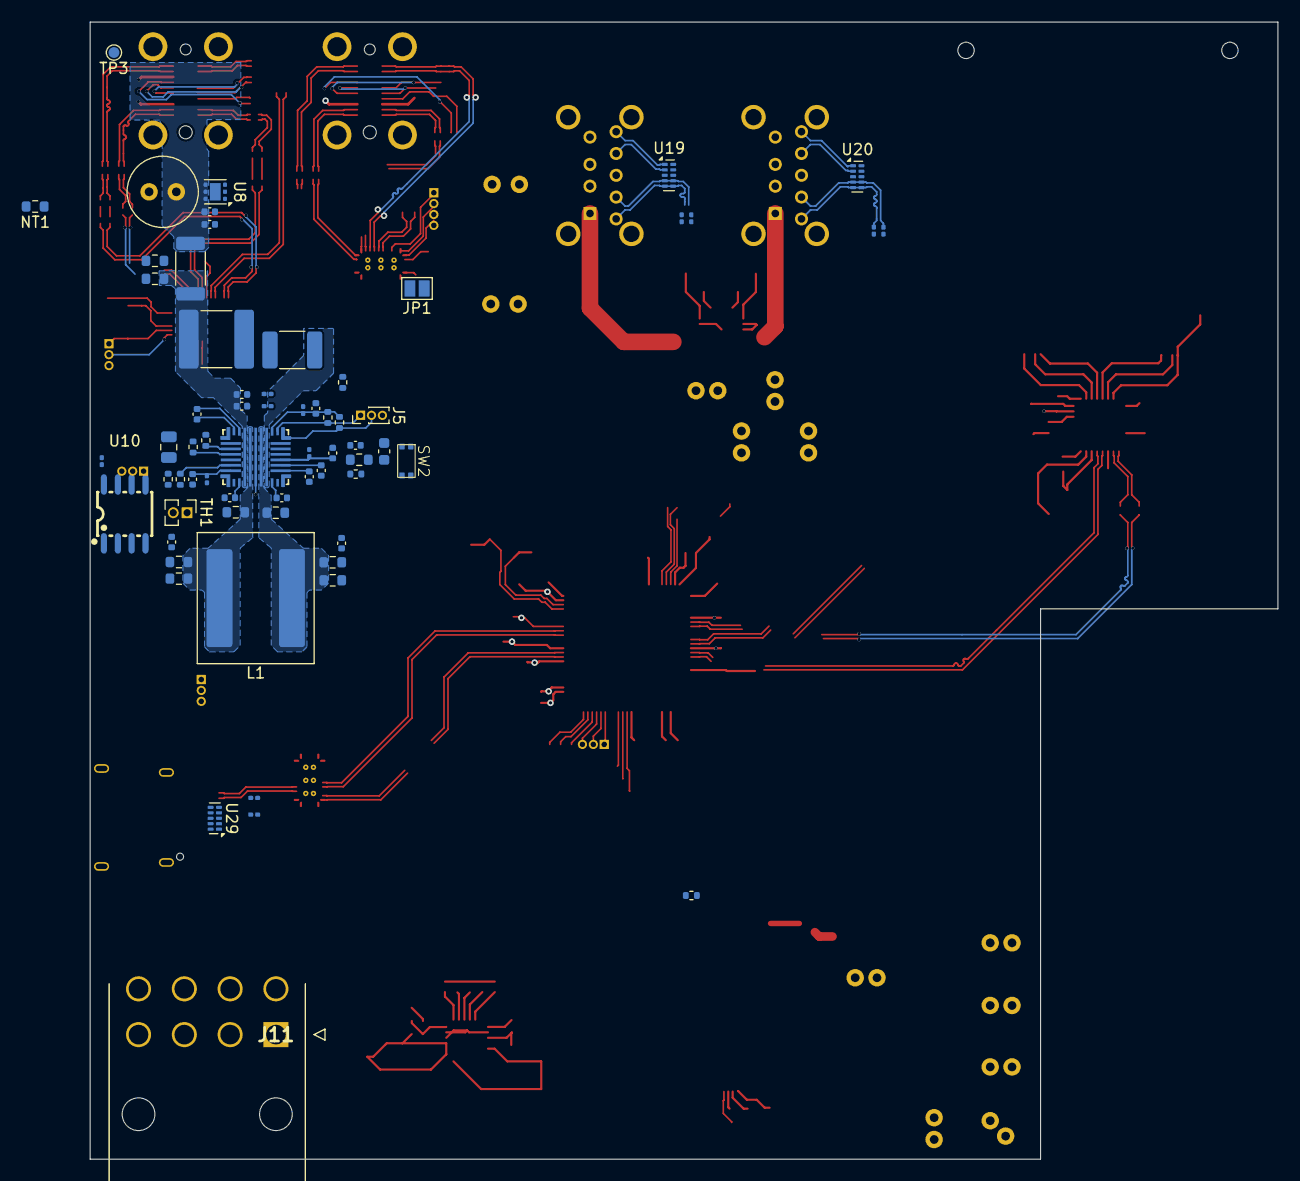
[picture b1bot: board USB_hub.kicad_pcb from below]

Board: 6 copper layers, 108.9 x 104.3 mm, 310 parts (65 on the bottom side), 236 nets.
